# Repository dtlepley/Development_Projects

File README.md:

# Development_Projects
Active Development Projects

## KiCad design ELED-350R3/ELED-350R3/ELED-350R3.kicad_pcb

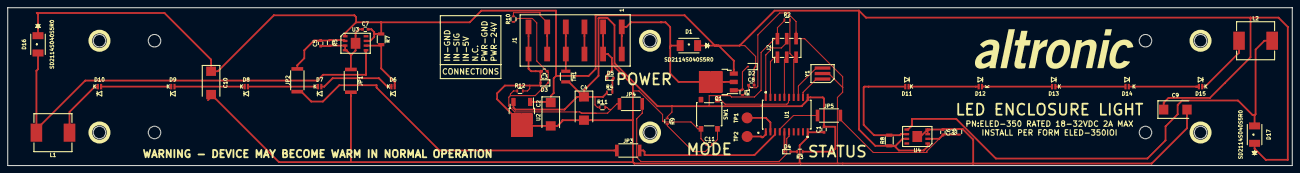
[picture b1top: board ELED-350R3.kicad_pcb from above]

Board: 2 copper layers, 350.0 x 43.0 mm, 59 parts (0 on the bottom side), 36 nets.

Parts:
C1, C3, C5, C6, C7, C8, C11: C; C_0603
C2, C4, C9, C10: CP; CP_Tantalum_Case-D_EIA-7343-31_Reflow
D1, D16, D17: SD2114S040S5R0
D2, D3: D_Zener; D_SOD-323
D4, D5: LED; D_0603
D6, D7, D8, D9, D10, D11, D12, D13, D14, D15: LED; Cree XD16
J1: Screw_Terminal_01x06; SPT-SMD 6 Pos Terminal
J2: AVR-ISP-6; Pin_Header_Straight_2x03_Pitch2.54mm_SMD
JP1, JP2, JP3, JP4, JP5: Jumper; R_2512
L1, L2: INDUCTOR; L_Vishay_IHLP-4040
Q1: Q_PMOS_GDS; TO-252-3_TabPin2
R1, R2, R3, R4, R5, R6, R9, R10, R11, R12: R; R_0603
R7, R8: R; R_1206
SW1: SW_Push; SW_SPST_B3S-1000
TH1: Thermistor_PTC; R_1210
TP1, TP2: TestPoint; Measurement_Point_Round-SMD-Pad_Big
U1: ATtiny1634-SU; ATTINY1634-SUR
U2: LM78M05_TO252; TO-252-2
U3, U4: ILD6070; PG-DSO-8-27
Y1: Resonator; AWSCR-CV

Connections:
+5V: C1.2, C4.1, J2.2, R2.1, R3.1, R4.1, R9.1, R11.1, TH1.2, U1.11, U2.3
+24V: C2.1, C7.2, C8.2, C9.1, C10.1, D1.1, D2.1, D16.1, D17.1, Q1.3, R7.1, R8.1, U2.1, U3.1, U3.7, U4.1, U4.7
A0: C3.1, D3.1, JP4.1, JP4.2, R10.1, R11.2, R12.1, U1.6
D2: C5.2, JP2.1, JP2.2, JP3.1, JP3.2, R5.1, U1.3, U3.2
D3: C6.2, JP5.1, JP5.2, R6.1, U1.4, U4.2
GND: C1.1, C2.2, C3.2, C4.2, C5.1, C6.1, C7.1, C8.1, C9.2, C10.2, C11.1, D3.2, D5.1, J1.2, J1.6, J2.6, JP1.1, JP1.2, R1.2, R5.2, R6.2, R12.2, SW1.2, U1.10, U2.2, U3.3, U3.4, U3.EP, U4.3, U4.4, U4.EP, Y1.2
unnamed: C11.2, R9.2, SW1.1, U1.15
unnamed: D2.2, Q1.1, R1.1
unnamed: D4.1, U1.5
unnamed: D4.2, R3.2
unnamed: D5.2, R4.2
unnamed: D6.1, D7.2
unnamed: D6.2, R7.2, U3.6
unnamed: D7.1, D8.2
unnamed: D8.1, D9.2
unnamed: D10.1, L1.1
unnamed: D9.1, D10.2
unnamed: D11.1, D12.2
unnamed: D11.2, R8.2, U4.6
unnamed: D12.1, D13.2
unnamed: D13.1, D14.2
unnamed: D14.1, D15.2
unnamed: D15.1, L2.1
unnamed: D16.2, L1.2, U3.5
unnamed: D17.2, L2.2, U4.5
unnamed: J1.4, TH1.1
unnamed: J1.5, R10.2
unnamed: J2.1, U1.19
unnamed: J2.3, U1.16
unnamed: J2.4, U1.20
unnamed: J2.5, R2.2, U1.14
unnamed: TP1.1, U1.2
unnamed: TP2.1, U1.1
unnamed: U1.12, Y1.1
unnamed: U1.13, Y1.3
VIN: D1.2, J1.1, Q1.2

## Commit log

2018-07-24 Added ELED-350R1 Project to GitHub
    Added ELED-350R1 Project to GitHub
2018-07-26 added LEDs
2018-08-24 symbol added
    added first symbol
2018-08-30 Added R2
2018-09-12 Finalized R2 of ELED-350
2018-09-28 added new projects
2018-12-11 Added air-speed control to lib
2018-12-12 Test
2019-02-02 Commited SAMD51 and AFR-1000
2019-02-28 l,kk

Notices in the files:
parts and their libraries:
Copyright 2016 Accelerated Designs. All rights reserved.
